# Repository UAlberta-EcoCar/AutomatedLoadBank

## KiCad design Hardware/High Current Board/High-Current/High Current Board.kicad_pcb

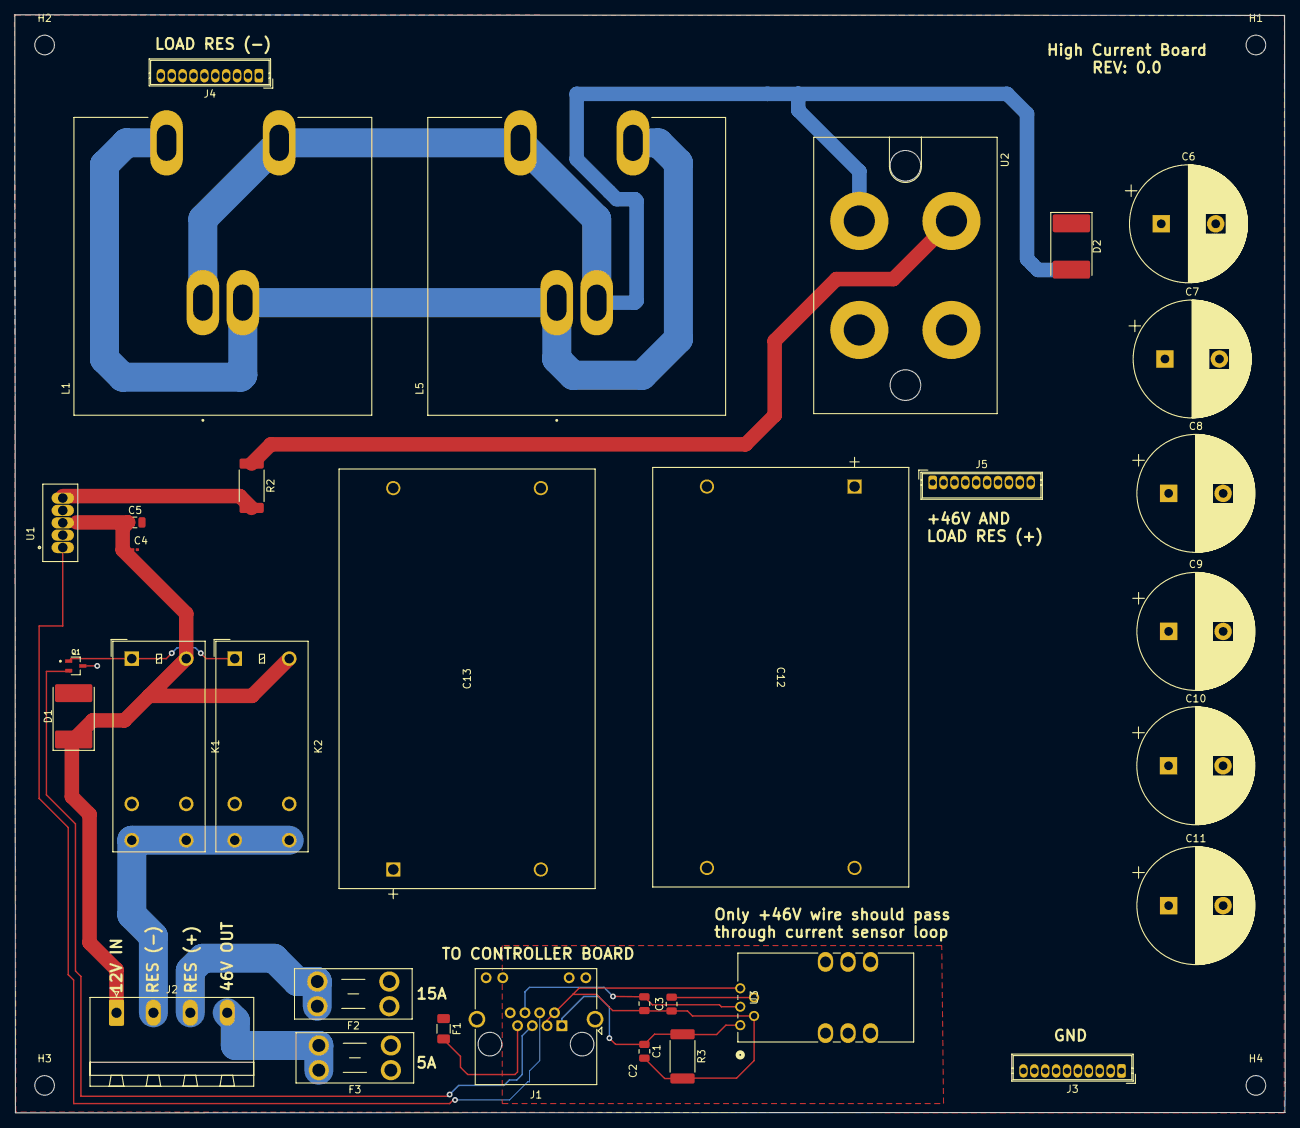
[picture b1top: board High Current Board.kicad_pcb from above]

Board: 2 copper layers, 174.9 x 151.1 mm, 37 parts (0 on the bottom side), 18 nets.

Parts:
C1, C3: 47nF; C_0805_2012Metric
C2: 4.7nF; C_0805_2012Metric
C4: 10uF; C_0201_0603Metric
C5: 0.1uF; C_0805_2012Metric
C6, C7, C8, C9, C10, C11: 6800uF; CP_Radial_D16.0mm_P7.50mm
C12, C13: 60uF; C4A-060_KEM
D1, D2: D_Schottky; D_3220_8050Metric
F1: Polyfuse; Fuse_1206_3216Metric
F2, F3: Fuse; Fuseholder_Blade_Mini_Keystone_3568
H1, H2, H3, H4: MountingHole; MountingHole_2.7mm_M2.5
J1: 8P8C_Shielded; RJ45_Amphenol_RJHSE538X
J2: Conn_01x04; PhoenixContact_MSTBA_2,5_4-G-5,08_1x04_P5.08mm_Horizontal
J3: GND; Wuerth_WR-WTB_64801011622_1x10_P1.50mm_Vertical
J4: Load Resistors Return; Wuerth_WR-WTB_64801011622_1x10_P1.50mm_Vertical
J5: +46V from Fuel Cell; Wuerth_WR-WTB_64801011622_1x10_P1.50mm_Vertical
K1, K2: G2RL-1A-E; Relay_SPST_Omron_G2RL-1A-E
L1, L5: L_Coupled; FIL_CMX1616Z171B-10
Q1: NMOS_Substrate; SOT65P210X100-3N
R2: 1R5; R_2512_6332Metric_Pad1.40x3.35mm_HandSolder
R3: 20k; R_2512_6332Metric_Pad1.40x3.35mm_HandSolder
U1: TC4421AVAT; TO170P1066X482X1572-5
U2: GENESIC_MBR200100CTS
U3: HO 25-P; HO 25-P_LEM

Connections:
+12V: C4.2, C5.1, D1.1 (K), J2.1, K1.A2, K2.A2, U1.3 (VDD)
+46V: C6.1, C7.1, C8.1, C9.1, C10.1, C11.1, C12.3, C12.4, C13.3, C13.4, D2.1 (K), F2.1, F3.1, J5.1
/3.3V: C1.1, J1.1, R3.1, U3.1 (+UC)
/3.3V_RETURN: C1.2, C2.1, C3.1, J1.2, J1.3, R3.2, U3.2 (0V), U3.5 (OCD)
/AIR_STARVE_RELAY: J1.5, Q1.2 (G)
/AIR_STARVE_RESISTORS: J2.2, K1.14, K2.14
/FUEL_CELL_CURRENT: C2.2, J1.6, U3.3 (VOUT)
/GATE_SIG: J1.4, U1.1 (VIN)
GATE_DRIVE: R2.1, U2.2 (G)
GND: C4.1, C5.2, C6.2, C7.2, C8.2, C9.2, C10.2, C11.2, C12.1, C12.2, C13.1, C13.2, J1.SH, J3.1, K1.13, K2.13, Q1.3 (S), U1.2 (GND), U1.4 (GND__1), U2.1 (S), U2.3 (S)
unnamed: D1.2 (A), K1.A1, K2.A1, Q1.1 (D)
unnamed: D2.2 (A), L1.1, L1.3, L5.2, L5.4, U2.4 (D)
unnamed: F1.2, J1.7
unnamed: F2.2, J2.3
unnamed: F3.2, J2.4
unnamed: J4.1, L1.2, L1.4, L5.1, L5.3
unnamed: R2.2, U1.5 (OUTPUT)
unnamed: C3.2, U3.4 (VREF)

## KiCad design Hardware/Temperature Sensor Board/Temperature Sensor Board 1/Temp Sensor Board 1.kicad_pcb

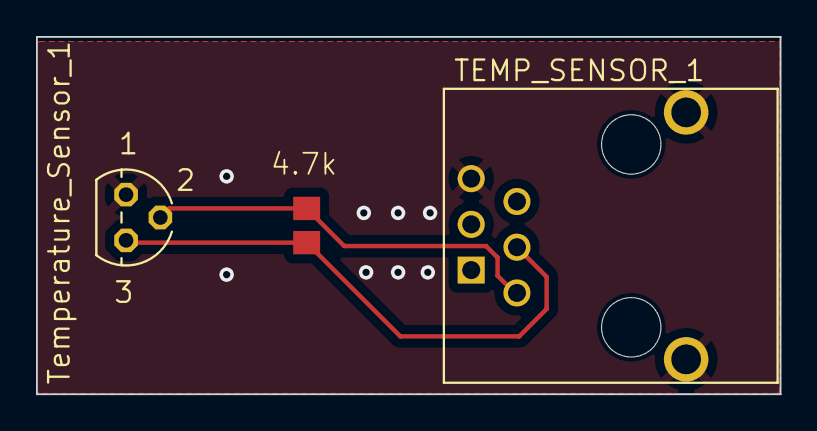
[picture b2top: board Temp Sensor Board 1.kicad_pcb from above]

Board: 2 copper layers, 41.3 x 19.9 mm, 3 parts (0 on the bottom side), 3 nets.

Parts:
4.7k: R; R0805
J1: 6P6C; 1734723-1_RJ11
U$1: Temperature_Sensor_1; TO92-3

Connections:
/DQ: 4.7k.1, J1.4, U$1.2 (DQ)
/GND: J1.3, J1.SH1, J1.SH2, U$1.1 (GND)
/VDD: 4.7k.2, J1.5, U$1.3 (VDD)

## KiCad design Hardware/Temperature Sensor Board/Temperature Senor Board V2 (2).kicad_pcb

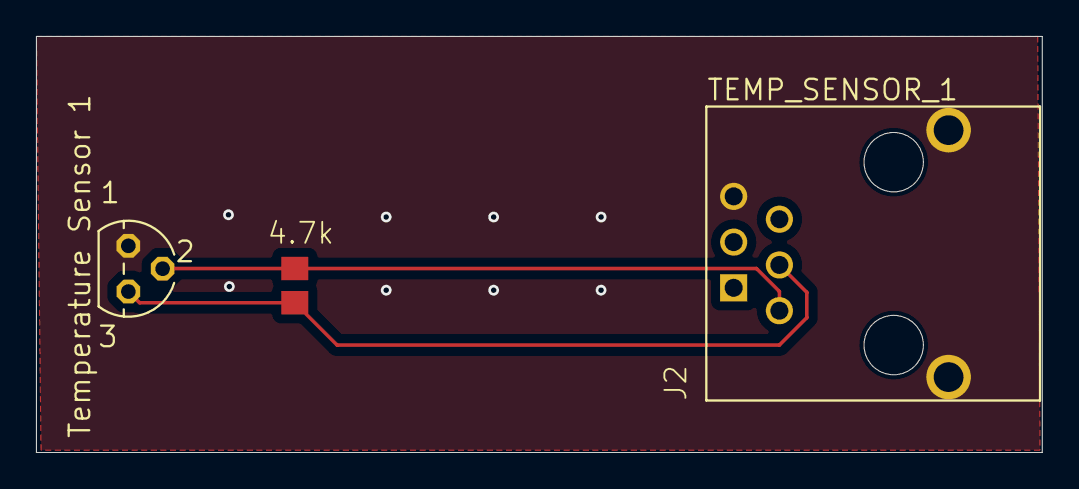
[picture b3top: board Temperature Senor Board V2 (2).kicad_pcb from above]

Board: 2 copper layers, 55.9 x 23.1 mm, 3 parts (0 on the bottom side), 3 nets.

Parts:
4.7k: R; R0805
J2: 6P6C; 1734723-1_RJ11
U$1: Temperature Sensor 1; TO92-3

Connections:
/DQ: 4.7k.1, J2.4, U$1.2 (DQ)
/GND: J2.3, J2.SH1, J2.SH2, U$1.1 (GND)
/VDD: 4.7k.2, J2.5, U$1.3 (VDD)

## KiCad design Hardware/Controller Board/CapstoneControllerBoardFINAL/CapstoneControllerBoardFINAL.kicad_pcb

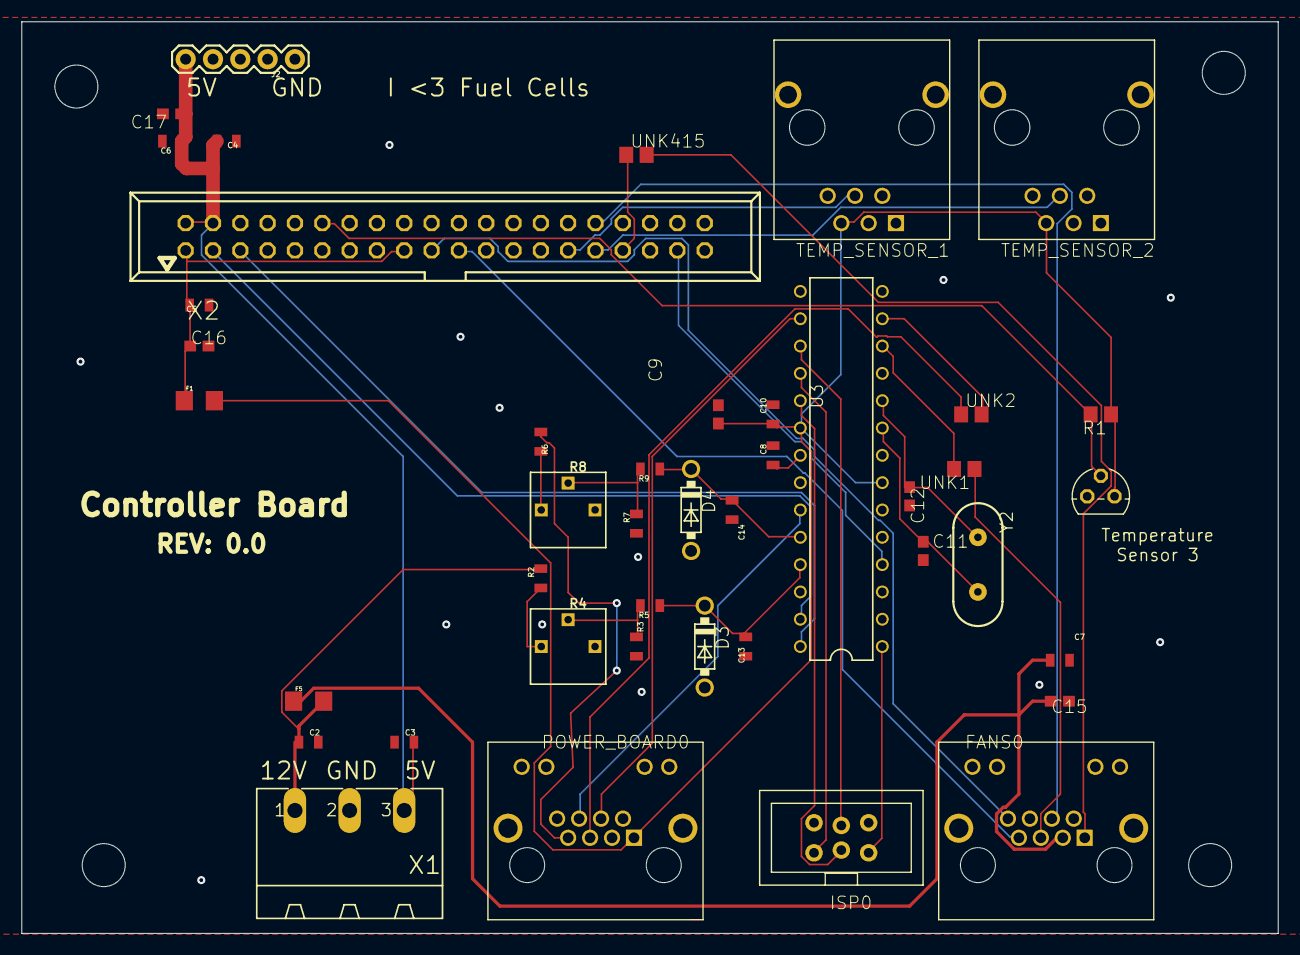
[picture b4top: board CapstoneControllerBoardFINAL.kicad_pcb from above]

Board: 2 copper layers, 116.8 x 84.8 mm, 48 parts (0 on the bottom side), 37 nets.

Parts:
@HOLE0, @HOLE1, @HOLE2, @HOLE3: (no value)
C2, C3, C4, C5, C6, C7, C8, C10, C13, C14: 0.1uF; 0805
C9, C15, C16, C17: 10uF; C0603
C11, C12: 22pF; C0603
D3, D4: 3.3V Zener; DO41-7.6
F1, F5: 1206
FANS0: ETHERNET; A122645-ND
FRAME2: FRAME-LETTERNO_PACKAGE; DUMMY
ISP0: AVRISP-BOX
J2: 1X05
POWER_BOARD0: ETHERNET; A122645-ND
R1: R0805
R2: 2.4k; 0805
R3: 1.2k; 0805
R4, R8: 0-5k; TRIM_POT
R5, R9: 5k; 0805
R6: 16k; 0805
R7: 1.3k; 0805
TEMP_SENSOR_1, TEMP_SENSOR_2: 5555140-6; 1734723-1_RJ11
U3: ATmega328P PDIP; PDIP-T28
U$2: DS18B; TO92
UNK1, UNK2: 110; R0805
UNK415: R0805
X1: MSTBA3
X2: 057-040-1
Y2: HC49US

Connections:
3.3V: C9.1, C10.1, F1.2, POWER_BOARD0.P$1, R1.1, TEMP_SENSOR_1.5, TEMP_SENSOR_2.5, U3.7, U3.20, U$2.3
12V: C2.1, F5.2, R2.2, X1.1
46V: POWER_BOARD0.P$7, R6.2
+5V: C3.2, C4.1, C6.1, C17.1, J2.5, X1.3, X2.2, X2.4
AIR_STARVE_RELAY: POWER_BOARD0.P$5, UNK2.1
DQ_1: TEMP_SENSOR_1.4, X2.29
DQ_2: TEMP_SENSOR_2.4, X2.31
DQ_3: R1.2, U$2.2, X2.12
EXTRA_PIN_1: FANS0.P$8, X2.19
EXTRA_PIN_2: FANS0.P$7, X2.21
FAN_PWM: FANS0.P$1, UNK415.2
FAN_PWM_ATMEL: FANS0.P$5, UNK1.1
FUEL_CELL_CURRENT1: POWER_BOARD0.P$6, U3.23
GATE_SIG: POWER_BOARD0.P$4, U3.16
GND: C2.2, C3.1, C4.2, C5.2, C6.2, C7.2, C8.2, C9.2, C10.2, C11.2, C12.2, C13.2, C14.2, C15.2, C16.2, C17.2, D3.A, D4.A, FANS0.P$2, FANS0.P$6, FANS0.P$13, FANS0.P$14, ISP0.6, J2.1, POWER_BOARD0.P$2, POWER_BOARD0.P$3, POWER_BOARD0.P$8, POWER_BOARD0.P$13, POWER_BOARD0.P$14, R3.1, R7.1, TEMP_SENSOR_1.3, TEMP_SENSOR_1.SH1, TEMP_SENSOR_1.SH2, TEMP_SENSOR_2.3, TEMP_SENSOR_2.SH1, TEMP_SENSOR_2.SH2, U3.8, U3.22, U$2.1, X1.2, X2.9, X2.14, X2.20, X2.25, X2.30, X2.39
LOAD_ENABLE: U3.4, X2.37
unnamed: C8.1, U3.21
unnamed: ISP0.1, U3.18
unnamed: ISP0.3, U3.19
unnamed: UNK415.1, X2.33
unnamed: R2.1, R4.1
unnamed: U3.12, UNK1.2
unnamed: C5.1, C16.1, F1.1, X2.1, X2.17
unnamed: R6.1, R8.1
unnamed: R3.2, R4.2, R5.2
unnamed: ISP0.4, U3.17
unnamed: C11.1, U3.9, Y2.2
unnamed: C12.1, U3.10, Y2.1
unnamed: R7.2, R8.2, R9.2
unnamed: C7.1, C15.1, F5.1, FANS0.P$3
unnamed: U3.13, UNK2.2
RESET: ISP0.5, U3.1
SCALED_BATT_V: C13.1, D3.C, R5.1, U3.25
SCALED_FUEL_CELL_V: C14.1, D4.C, R9.1, U3.24
SCL: U3.28, X2.5
SDA: U3.27, X2.3
WARNING_LED: FANS0.P$4, X2.32

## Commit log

2019-11-16 removed duplicate files :^)
2019-11-16 test changes were made to learn git
2020-03-14 Updated GUI Directory
2023-11-25 no changes
2023-12-02 editing
2023-12-02 to92-package
2023-12-02 work on temp sensor board
2023-12-02 Changed Schematic for Temp Sens Board
2023-12-02 Gerber File Changed
2023-12-03 Added File for Temperature Sensor Board 1 and Temperature Sensor Board 2
2023-12-28 random push
2023-12-29 some change s
2024-01-01 edit
2024-01-01 complete gerber for temp sensors
2024-01-04 proj create
2024-01-04 sch capture
2024-01-04 sch capture 2
2024-01-05 started new schematicccccccc:)))))))
2024-01-06 final edit
2024-01-06 Updated Schematic
2024-01-07 PCB Update for the schematic
2024-01-07 final update
2024-01-07 PCB Updated
2024-01-11 PCB Update - HC
2024-01-11 PCB Update 1.0
    Needs a Revision Check and we good
2024-01-11 Text update
